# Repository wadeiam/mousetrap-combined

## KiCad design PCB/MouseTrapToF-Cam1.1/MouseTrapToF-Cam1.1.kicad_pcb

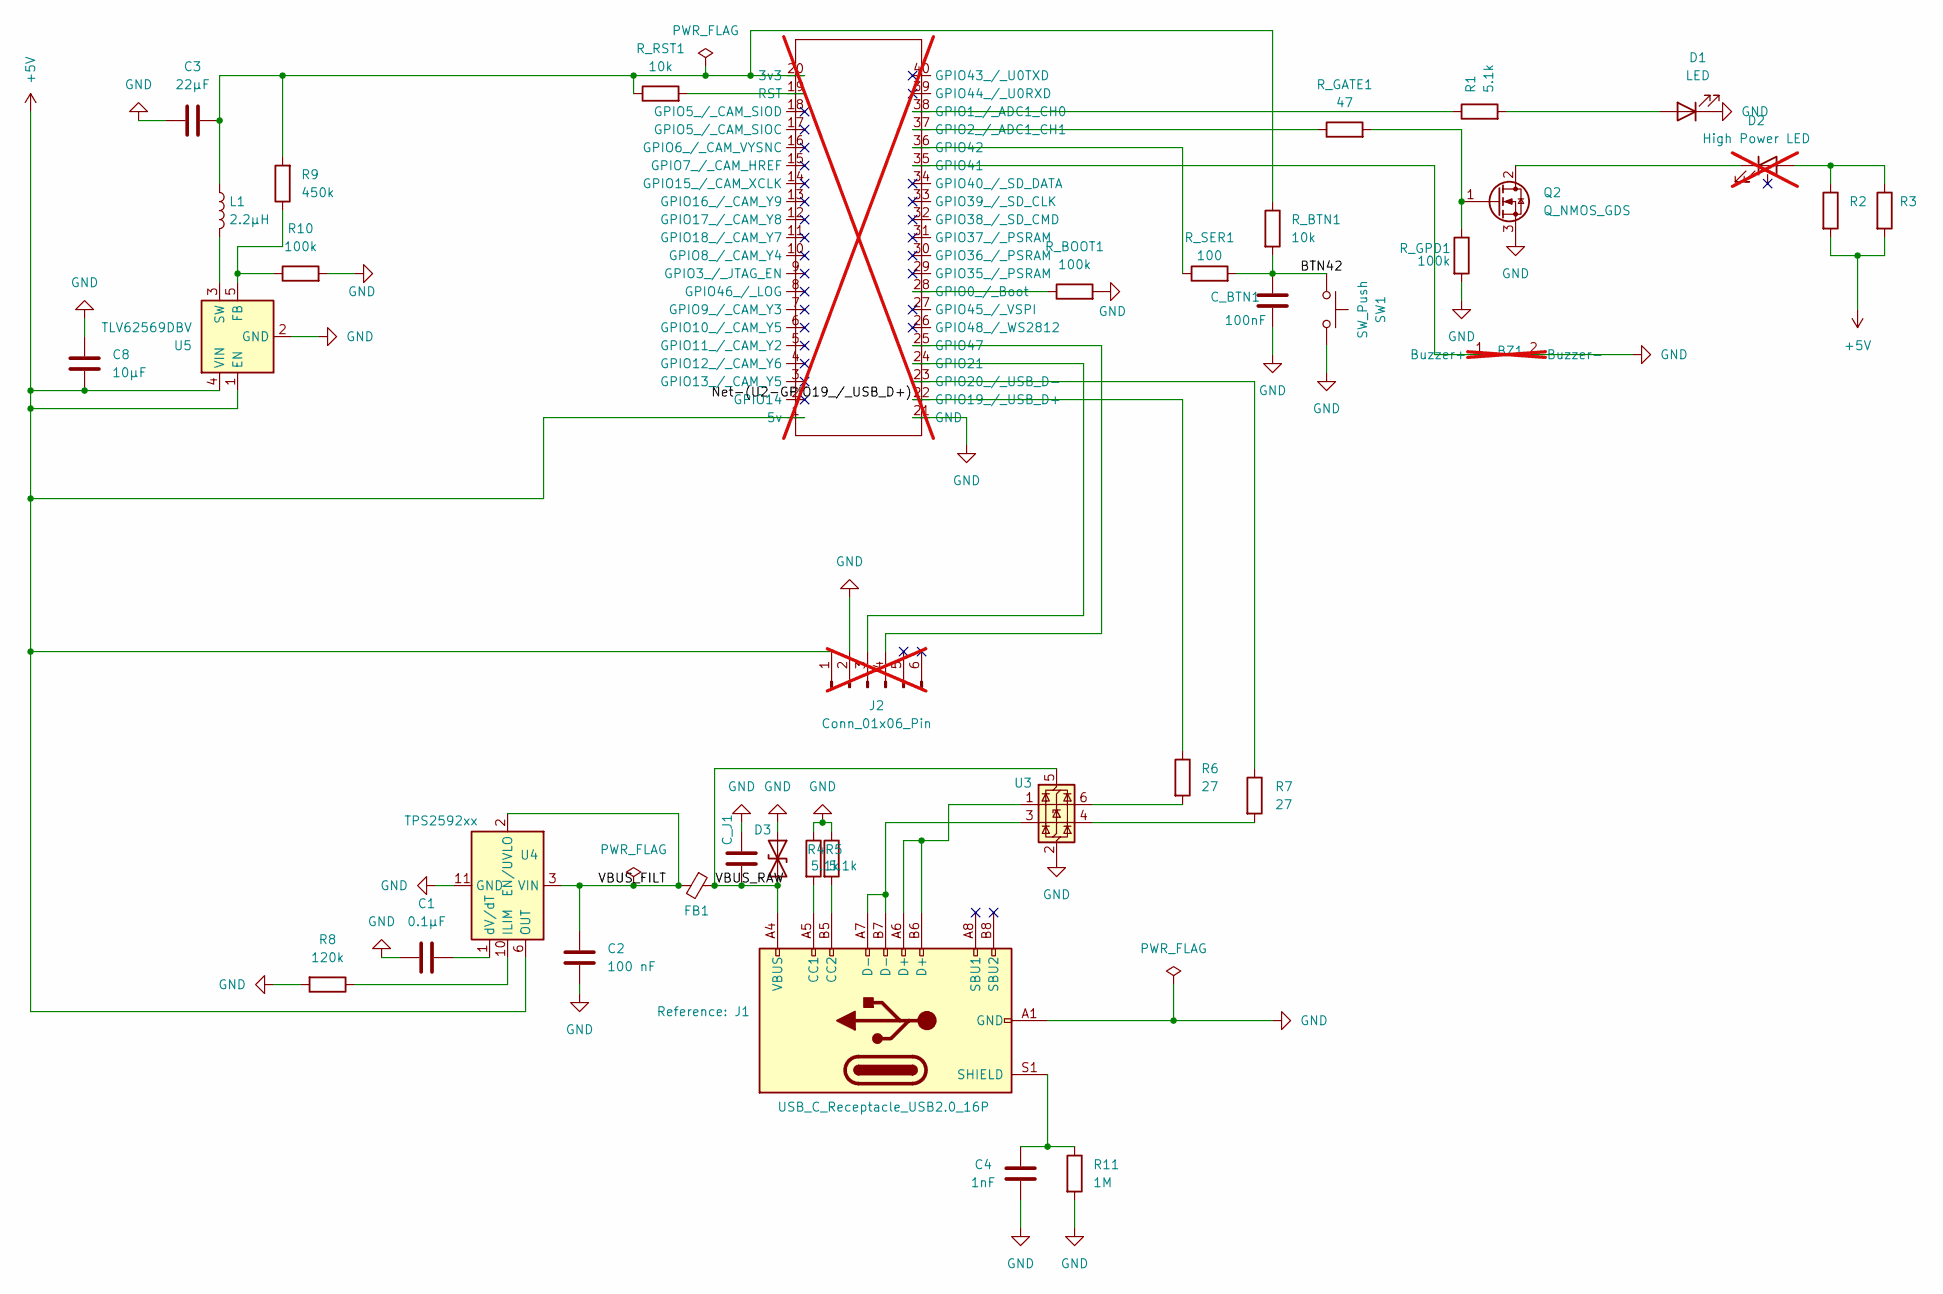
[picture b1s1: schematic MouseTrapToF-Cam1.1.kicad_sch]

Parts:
BZ1: BUZZER_THT_D12MM_P5MM; not fitted
C1: 0.1µF; C_1206_3216Metric
C2: 100 nF; C_0603_1608Metric
C3: 22µF; C_0805_2012Metric
C4: 1nF; C_0603_1608Metric
C8: 10µF; C_0805_2012Metric
C_BTN1: 100nF; C_0603_1608Metric
C_J1: 1µF; C_0603_1608Metric
D1: LED; LED_D5.0mm
D2: High Power LED; LED_1W_3W_R8; not fitted
D3: SMF5.0CA (TVS); D_SOD-123F
FB1: FerriteBead_Small; L_0603_1608Metric
J1: USB_C_Receptacle_USB2.0_16P; USB_C_Receptacle_HRO_TYPE-C-31-M-12
J2: Conn_01x06_Pin; VL6180X_FlatPads_1x06_P2.54_SMD; not fitted
L1: 2.2µH; L_Coilcraft_XAL4020-XXX
Q2: Q_NMOS_GDS; TO-252-2
R1: 5.1k; R_0603_1608Metric
R2, R3: 10; R_0603_1608Metric
R4, R5: 5.1k; R_0402_1005Metric
R6, R7: 27; R_0603_1608Metric
R8: 120k; R_0603_1608Metric
R9: 450k; R_0402_1005Metric
R10: 100k; R_0402_1005Metric
R11: 1M; R_0603_1608Metric
R_BOOT1: 100k; R_0603_1608Metric
R_BTN1: 10k; R_0603_1608Metric
R_GATE1: 47; R_0603_1608Metric
R_GPD1: 100k; R_0603_1608Metric
R_RST1: 10k; R_0603_1608Metric
R_SER1: 100; R_0603_1608Metric
SW1: SW_Push; SW_PUSH_1P1T_6x3.5mm_H5.0_APEM_MJTP1250
U2: ESP32-S3-CAM_Base_2x20; not fitted
U3: USBLC6-2SC6; SOT-23-6
U4: TPS2592xx; VSON-10-1EP_3x3mm_P0.5mm_EP1.65x2.4mm_ThermalVias
U5: TLV62569DBV; SOT-23-5

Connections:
+5V: C8.1, J2.1, R2.2, R3.2, U2.1 (5v), U4.6 (OUT), U4.7 (OUT), U4.8 (OUT), U5.1 (EN), U5.4 (VIN)
/BTN42: C_BTN1.1, R_BTN1.2, R_SER1.2, SW1.1
/VBUS_FILT: C2.1, FB1.2, U4.2 (EN/UVLO), U4.3 (VIN), U4.4 (VIN), U4.5 (VIN)
/VBUS_RAW: C_J1.1, D3.2 (A2), FB1.1, J1.A4 (VBUS), J1.A9 (VBUS), J1.B4 (VBUS), J1.B9 (VBUS), U3.5 (VBUS)
unnamed: BZ1.1 (Buzzer+), U2.35 (GPIO41)
unnamed: D1.2 (A), R1.2
unnamed: D2.2 (A), R2.1, R3.1
unnamed: D2.1 (K), Q2.2 (D)
unnamed: J1.A5 (CC1), R4.2
unnamed: J1.B5 (CC2), R5.2
unnamed: J1.A6 (D+), J1.B6 (D+), U3.1 (I/O1)
unnamed: J1.A7 (D-), J1.B7 (D-), U3.3 (I/O2)
unnamed: C4.1, J1.S1 (SHIELD), R11.1
unnamed: J2.3, U2.24 (GPIO21)
unnamed: J2.4, U2.25 (GPIO47)
unnamed: Q2.1 (G), R_GATE1.2, R_GPD1.1
unnamed: R6.2, U3.6 (I/O1)
unnamed: R7.2, U3.4 (I/O2)
unnamed: C3.2, L1.1, R9.2, R_BTN1.1, R_RST1.1, U2.20 (3v3)
unnamed: R_BOOT1.1, U2.28 (GPIO0_/_Boot)
unnamed: R1.1, U2.38 (GPIO1_/_ADC1_CH0)
unnamed: R_GATE1.1, U2.37 (GPIO2_/_ADC1_CH1)
unnamed: R7.1, U2.23 (GPIO20_/_USB_D-)
unnamed: R_SER1.1, U2.36 (GPIO42)
unnamed: R_RST1.2, U2.19 (RST)
unnamed: R8.1, U4.10 (ILIM)
unnamed: C1.2, U4.1 (dV/dT)
unnamed: R9.1, R10.1, U5.5 (FB)
unnamed: L1.2, U5.3 (SW)

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
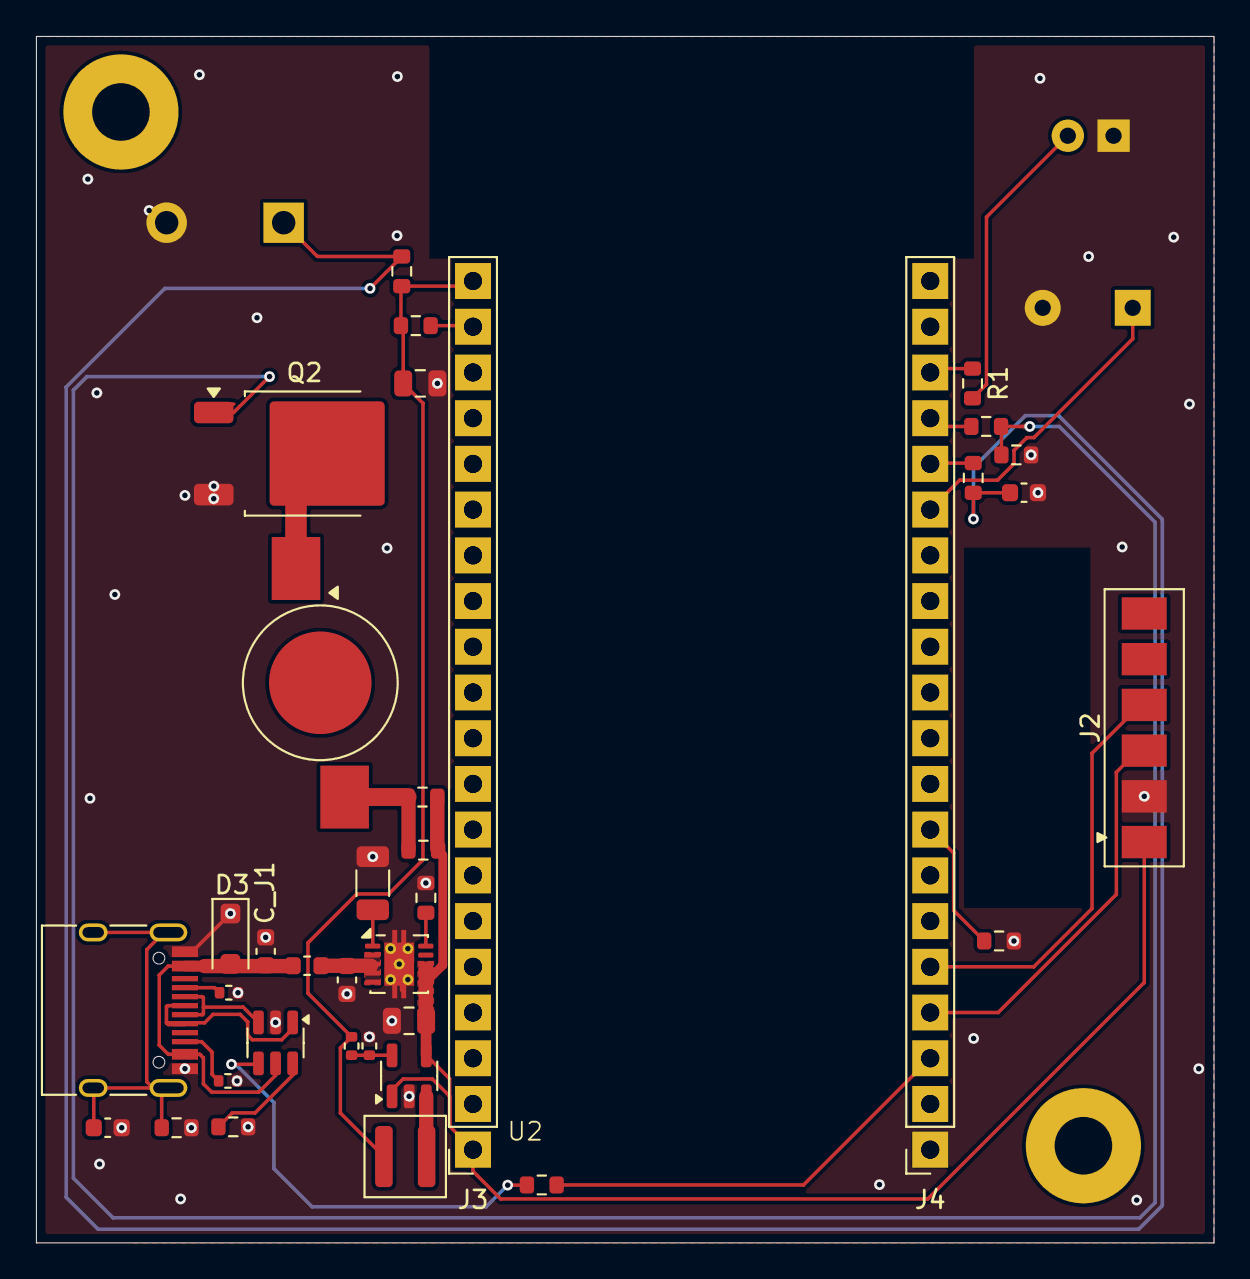
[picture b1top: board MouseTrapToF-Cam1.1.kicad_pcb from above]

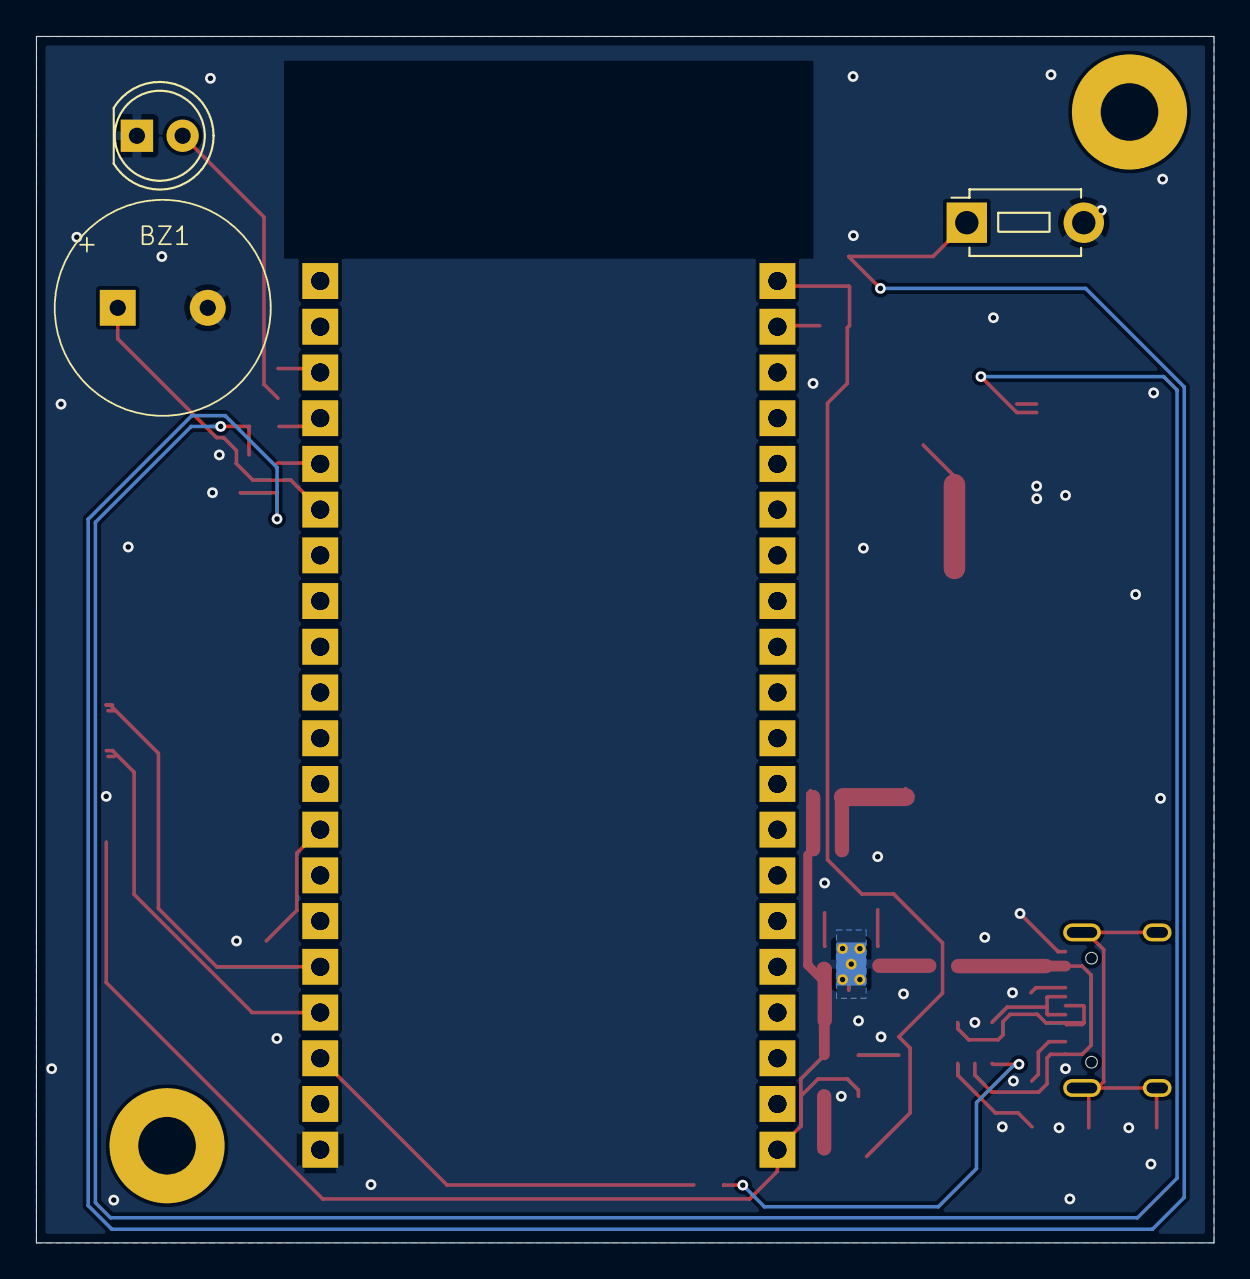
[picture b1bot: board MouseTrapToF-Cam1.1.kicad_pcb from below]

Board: 2 copper layers, 65.4 x 67.0 mm, 40 parts (3 on the bottom side), 30 nets.

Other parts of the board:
J3, J4: PinSocket_1x20_P2.54mm_Vertical

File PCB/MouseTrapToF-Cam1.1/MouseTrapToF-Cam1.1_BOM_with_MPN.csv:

Designator,Footprint,Quantity,Comment,Manufacturer Part Number (MPN),DNP
D3,D_SOD-123F,1,SMF5.0CA (TVS),SMF5.0CA,
U3,SOT-23-6,1,USBLC6-2SC6,USBLC6-2SC6,
"R7,R6",R_0603_1608Metric,2,27,RC0603FR-0727RL,
R11,R_0603_1608Metric,1,1M,RC0603FR-071M0L,
FB1,L_0603_1608Metric,1,FerriteBead_Small,BLM18PG471SN1D,
"R5,R4",R_0402_1005Metric,2,5.1k,RC0402FR-0751KL,
C_J1,C_0603_1608Metric,1,1µF,,
C2,C_0603_1608Metric,1,100 nF,,
C4,C_0603_1608Metric,1,1nF,CL10B102KB8NNNC,
U4,VSON-10-1EP_3x3mm_P0.5mm_EP1.65x2.4mm_ThermalVias,1,TPS2592xx,TPS25921ADRBR,
J1,USB_C_Receptacle_HRO_TYPE-C-31-M-12,1,USB_C_Receptacle_USB2.0_16P,TYPE-C-31-M-12,
"R_GPD1,R_BOOT1",R_0603_1608Metric,2,100k,RC0603FR-07100KL,
R_GATE1,R_0603_1608Metric,1,47,RC0603FR-0747RL,
R9,R_0402_1005Metric,1,450k,RC0402FR-07450KL,
R10,R_0402_1005Metric,1,100k,RC0402FR-07100KL,
"R3,R2",R_0603_1608Metric,2,10,RC0603FR-0710RL,
L1,L_Coilcraft_XAL4020-XXX,1,2.2µH,XAL4020-222MEB,
C3,C_0805_2012Metric,1,22µF,,
R8,R_0603_1608Metric,1,120k,RC0603FR-07120KL,
"R_RST1,R_BTN1",R_0603_1608Metric,2,10k,RC0603FR-0710KL,
C_BTN1,C_0603_1608Metric,1,100nF,CL10B104KB8NNNC,
C8,C_0805_2012Metric,1,10µF,,
U5,SOT-23-5,1,TLV62569DBV,TLV62569DBVR,
SW1,SW_PUSH_1P1T_6x3.5mm_H5.0_APEM_MJTP1250,1,SW_Push,MJTP1250,
D1,LED_D5.0mm,1,LED,WP7113ID,
C1,C_1206_3216Metric,1,0.1µF,,
R1,R_0603_1608Metric,1,R,RC0603FR-07RRL,
R_SER1,R_0603_1608Metric,1,100,RC0603FR-07100RL,
Q2,TO-252-2,1,Q_NMOS_GDS,IRLR7843TRPBF,
U2,ESP32-S3-CAM_Base_2x20,1,~,,Yes
J2,VL6180X_FlatPads_1x06_P2.54_SMD,1,Conn_01x06_Pin,,Yes
D2,LED_1W_3W_R8,1,High Power LED,,Yes

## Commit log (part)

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2025-12-01 Fix mobile app API URL for preview builds, add google-services.json
2025-12-01 Add better error messages to mobile app login
2025-12-01 Enable cleartext HTTP traffic for Android
2025-12-01 Add expo-build-properties for Android cleartext
2026-04-12 Add YOLOv8n training notebook for camera-trap rodent detection
2026-04-12 Fix LILA dataset URLs — use verified GCP endpoints for YOLO training notebook
2026-04-12 Fix YOLO notebook CPU/GPU detection + add ML performance dashboard
    - Auto-detect device (CPU vs GPU) instead of hardcoding device=0
    - Reduce sample to ~50 images for pipeline validation on CPU
    - Add /api/classification/ml-performance JSON endpoint
    - Rewrite /api/classification/debug dashboard with per-device metrics
2026-06-13 Created using Colab
